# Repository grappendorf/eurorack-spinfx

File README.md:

Eurorack SpinFX
===============

An effects module based on the [Spin FV-1](http://www.spinsemi.com/products.html) IC.

The circuit is built from the reference design in the 
[data sheet](http://www.spinsemi.com/Products/datasheets/spn1001/FV-1.pdf) with some 
standard input and output signal level translation. I've also added a slightly over-engineered 
program number display.

More information can be found on the
[project website](http://www.grappendorf.net/projects/eurorack/eurorack-spinfx.html).

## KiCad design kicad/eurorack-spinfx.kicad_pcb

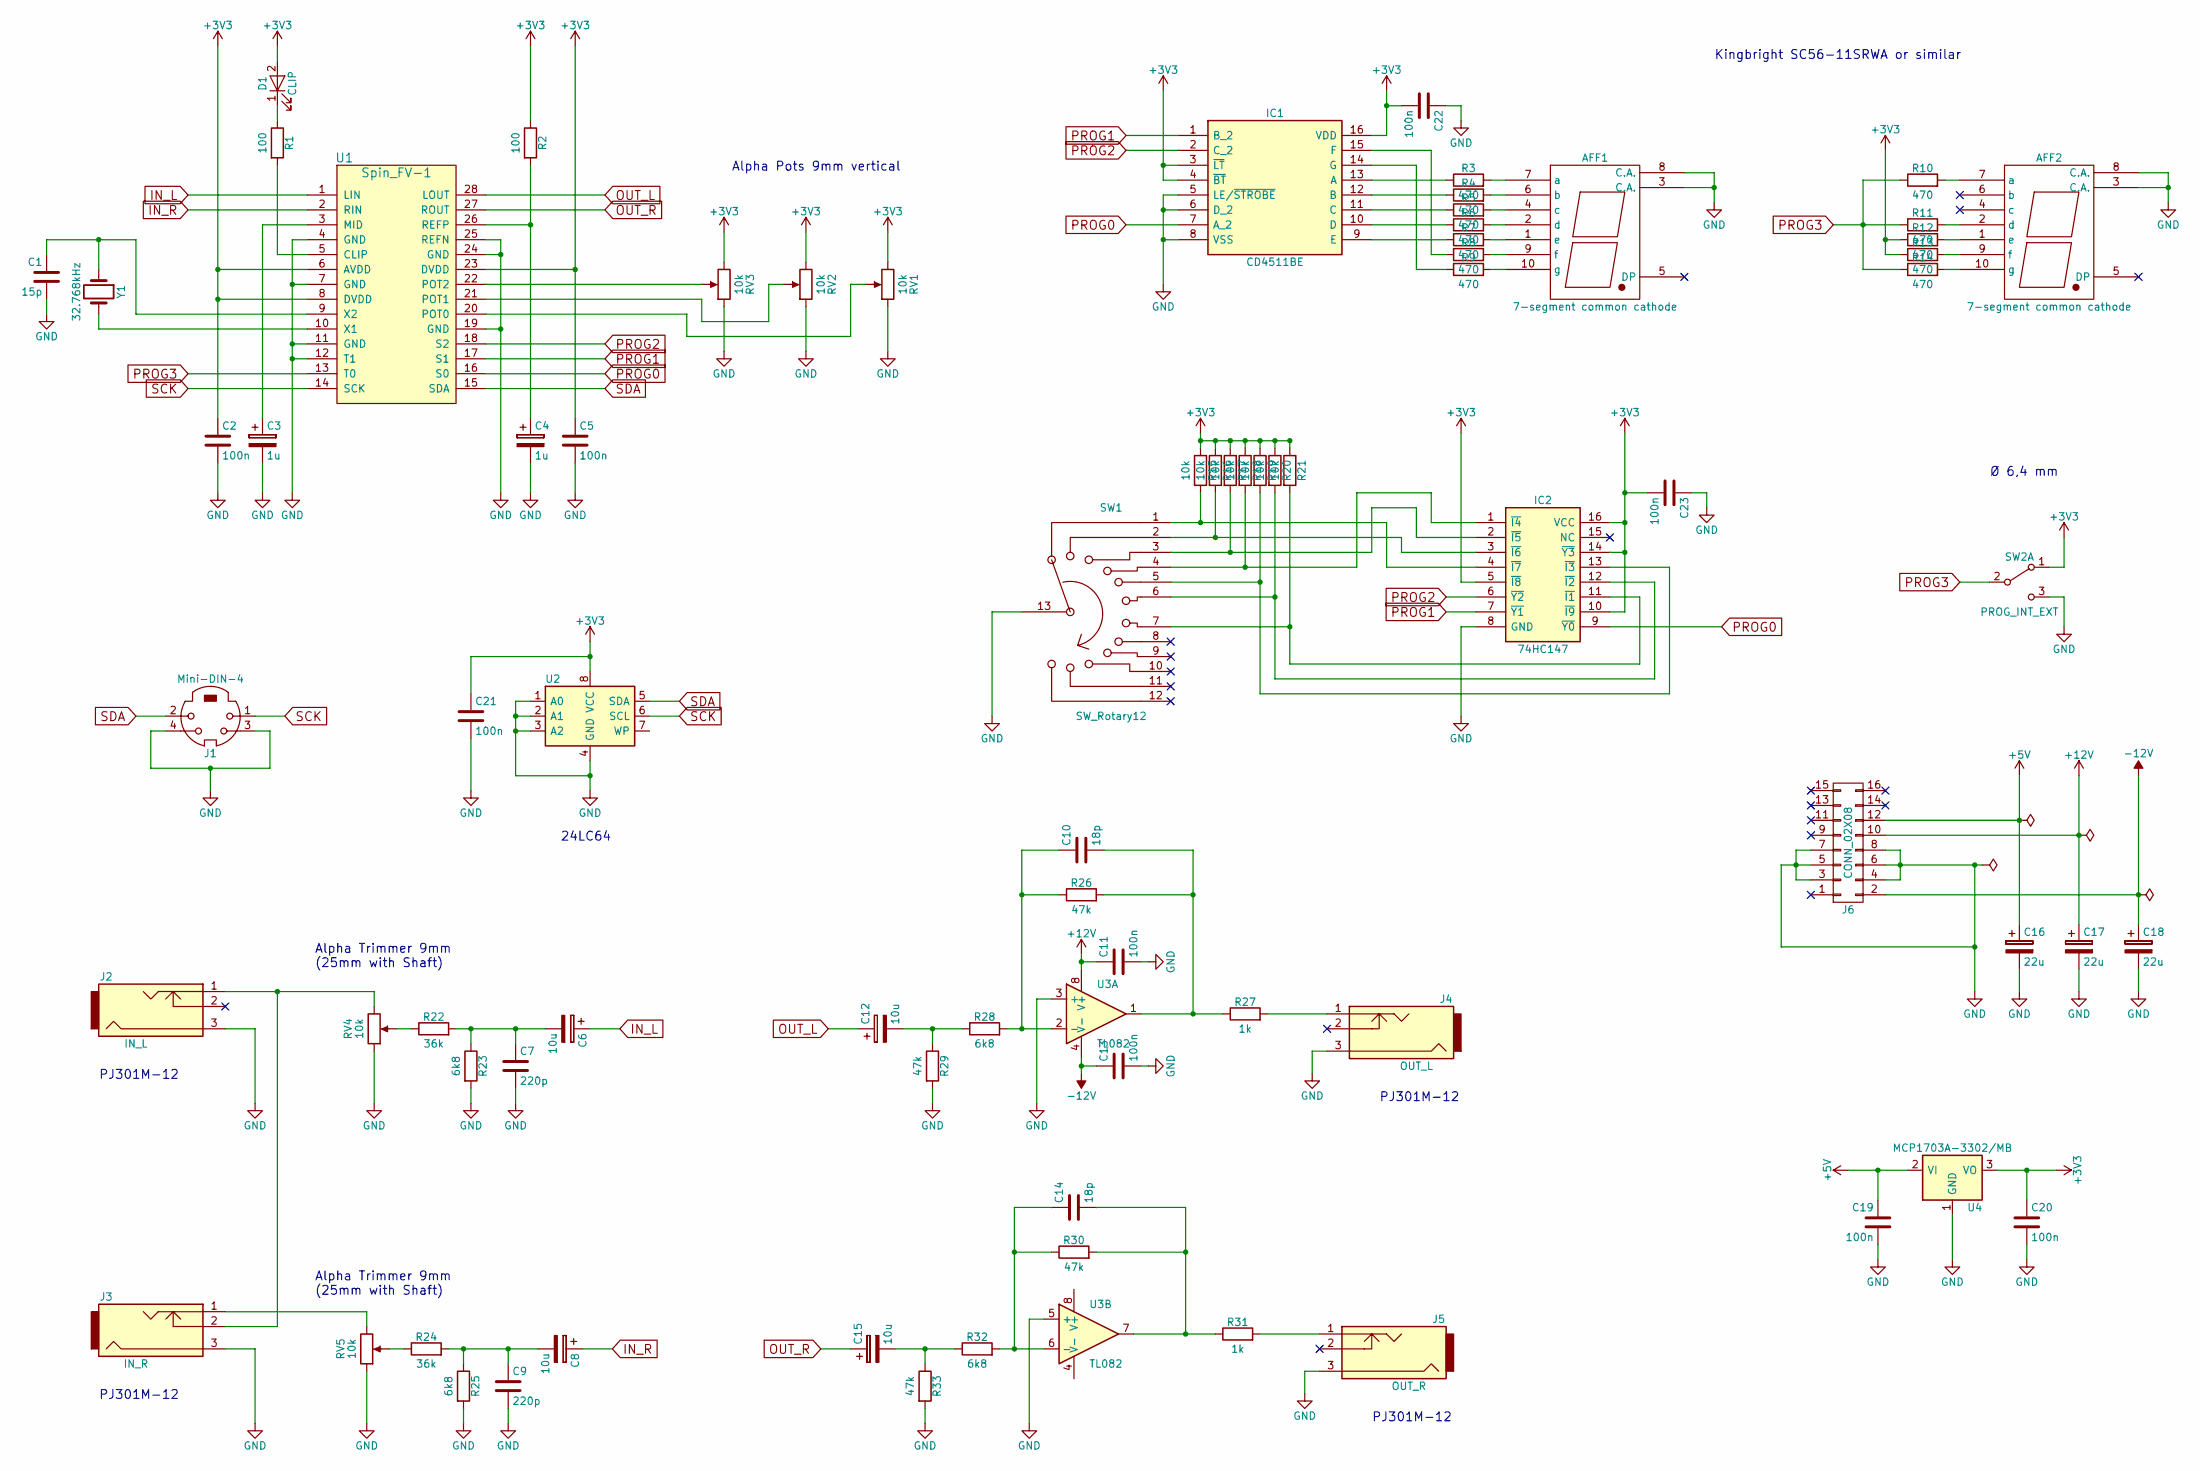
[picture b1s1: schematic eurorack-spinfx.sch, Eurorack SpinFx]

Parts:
AFF1, AFF2: 7-segment common cathode; 7SegmentLED_LTS6760_LTS6780
C1: 15p; C_1206
C2, C5, C11, C13, C19, C20, C21, C22, C23: 100n; C_1206
C3, C4: 1u; CP_Elec_4x5.8
C6, C8, C12, C15: 10u; CP_Elec_4x5.8
C7, C9: 220p; C_1206
C10, C14: 18p; C_1206
C16, C17, C18: 22u; CP_Elec_6.3x5.8
D1: CLIP; LED_D3.0mm
IC1: CD4511BE; SOIC-16_3.9x9.9mm_Pitch1.27mm; Manufacturer_Part_Number CD4511BE
IC2: 74HC147; SOIC-16_3.9x9.9mm_Pitch1.27mm; Manufacturer_Part_Number CD74HC147EE4
J1: Mini-DIN-4; Mini_Din_4
J2: IN_L; PJ301M-12
J3: IN_R; PJ301M-12
J4: OUT_L; PJ301M-12
J5: OUT_R; PJ301M-12
J6: CONN_02X08; Eurorack_Power_2x8_SMD
R1, R2: 100; R_1206
R3, R4, R5, R6, R7, R8, R9, R10, R11, R12, R13, R14: 470; R_1206
R15, R16, R17, R18, R19, R20, R21: 10k; R_1206
R22, R24: 36k; R_1206
R23, R25, R28, R32: 6k8; R_1206
R26, R29, R30, R33: 47k; R_1206
R27, R31: 1k; R_1206
RV1, RV2, RV3: 10k; Alpha_9mm_Pot
RV4, RV5: 10k; Alpha_9mm_Trimmer_25mm_with_Shaft
SW1: SW_Rotary12; ROTARY_SWITCH_LORLINCK1049
SW2: PROG_INT_EXT; Switch_Eledis_1x_On_On
U1: Spin_FV-1; SOIC-28W_7.5x17.9mm_Pitch1.27mm
U2: 24LC64; SO-8_5.3x6.2mm_Pitch1.27mm
U3: TL082; SO-8_5.3x6.2mm_Pitch1.27mm
U4: MCP1703A-3302/MB; SOT-89-3
Y1: 32.768kHz; Crystal_C26-LF_d2.1mm_l6.5mm_Horizontal_1EP_style1

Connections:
+3V3: C2.1, C5.1, C20.1, C21.1, C22.2, C23.2, D1.2 (A), IC1.3 (~LT), IC1.4 (~BT), IC1.16 (VDD), IC2.5 (~I8), IC2.10 (~I9), IC2.14 (~Y3), IC2.16 (VCC), R2.1, R12.1, R13.1, R15.1, R16.1, R17.1, R18.1, R19.1, R20.1, R21.1, RV1.3, RV2.3, RV3.3, SW2.1 (A), U1.6 (AVDD), U1.8 (DVDD), U1.23 (DVDD), U2.8 (VCC), U4.3 (VO)
+5V: C16.1, C19.1, J6.12, U4.2 (VI)
+12V: C11.1, C17.1, J6.10, U3.8 (V+)
-12V: C13.1, C18.1, J6.2, U3.4 (V-)
GND: AFF1.3 (C.A.), AFF1.8 (C.A.), AFF2.3 (C.A.), AFF2.8 (C.A.), C1.2, C2.2, C3.2, C4.2, C5.2, C7.2, C9.2, C11.2, C13.2, C16.2, C17.2, C18.2, C19.2, C20.2, C21.2, C22.1, C23.1, IC1.5 (LE/~STROBE), IC1.6 (D_2), IC1.8 (VSS), IC2.8 (GND), J1.3, J1.4, J2.3, J3.3, J4.3, J5.3, J6.3, J6.4, J6.5, J6.6, J6.7, J6.8, R23.2, R25.2, R29.2, R33.2, RV1.1, RV2.1, RV3.1, RV4.1, RV5.1, SW1.13, SW2.3 (C), U1.4 (GND), U1.7 (GND), U1.11 (GND), U1.12 (T1), U1.19 (GND), U1.24 (GND), U1.25 (REFN), U2.1 (A0), U2.2 (A1), U2.3 (A2), U2.4 (GND), U3.3 (+), U3.5 (+), U4.1 (GND)
IN_L: C6.1, U1.1 (LIN)
IN_R: C8.1, U1.2 (RIN)
unnamed: AFF1.1 (e), R7.2
unnamed: AFF1.2 (d), R6.2
unnamed: AFF1.4 (c), R5.2
unnamed: AFF1.6 (b), R4.2
unnamed: AFF1.7 (a), R3.2
unnamed: AFF1.9 (f), R8.2
unnamed: AFF1.10 (g), R9.2
unnamed: AFF2.1 (e), R12.2
unnamed: AFF2.2 (d), R11.2
unnamed: AFF2.7 (a), R10.2
unnamed: AFF2.9 (f), R13.2
unnamed: AFF2.10 (g), R14.2
unnamed: C1.1, U1.9 (X2), Y1.1
unnamed: C3.1, U1.3 (MID)
unnamed: C4.1, R2.2, U1.26 (REFP)
unnamed: C6.2, C7.1, R22.2, R23.1
unnamed: C8.2, C9.1, R24.2, R25.1
unnamed: C10.1, R26.1, R28.2, U3.2 (-)
unnamed: C10.2, R26.2, R27.1, U3.1
unnamed: C12.2, R28.1, R29.1
unnamed: C14.1, R30.1, R32.2, U3.6 (-)
unnamed: C14.2, R30.2, R31.1, U3.7
unnamed: C15.2, R32.1, R33.1
unnamed: D1.1 (K), R1.1
unnamed: IC1.9 (E), R7.1
unnamed: IC1.10 (D), R6.1
unnamed: IC1.11 (C), R5.1
unnamed: IC1.12 (B), R4.1
unnamed: IC1.13 (A), R3.1
unnamed: IC1.14 (G), R9.1
unnamed: IC1.15 (F), R8.1
unnamed: IC2.1 (~I4), R18.2, SW1.4
unnamed: IC2.2 (~I5), R17.2, SW1.3
unnamed: IC2.3 (~I6), R16.2, SW1.2
unnamed: IC2.4 (~I7), R15.2, SW1.1
unnamed: IC2.11 (~I1), R21.2, SW1.7
unnamed: IC2.12 (~I2), R20.2, SW1.6
unnamed: IC2.13 (~I3), R19.2, SW1.5
unnamed: J2.1, J3.2, RV4.3
unnamed: J3.1, RV5.3
unnamed: J4.1, R27.2
unnamed: J5.1, R31.2
unnamed: R1.2, U1.5 (CLIP)
unnamed: R22.1, RV4.2
unnamed: R24.1, RV5.2
unnamed: RV1.2, U1.20 (POT0)
unnamed: RV2.2, U1.21 (POT1)
unnamed: RV3.2, U1.22 (POT2)
unnamed: U1.10 (X1), Y1.2
OUT_L: C12.1, U1.28 (LOUT)
OUT_R: C15.1, U1.27 (ROUT)
PROG0: IC1.7 (A_2), IC2.9 (~Y0), U1.16 (S0)
PROG1: IC1.1 (B_2), IC2.7 (~Y1), U1.17 (S1)
PROG2: IC1.2 (C_2), IC2.6 (~Y2), U1.18 (S2)
PROG3: R10.1, R11.1, R14.1, SW2.2 (B), U1.13 (T0)
SCK: J1.1, U1.14 (SCK), U2.6 (SCL)
SDA: J1.2, U1.15 (SDA), U2.5 (SDA)

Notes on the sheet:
Alpha Trimmer 9mm (25mm with Shaft)
Alpha Pots 9mm vertical
Kingbright SC56-11SRWA or similar
Ø 6,4 mm
PJ301M-12
24LC64

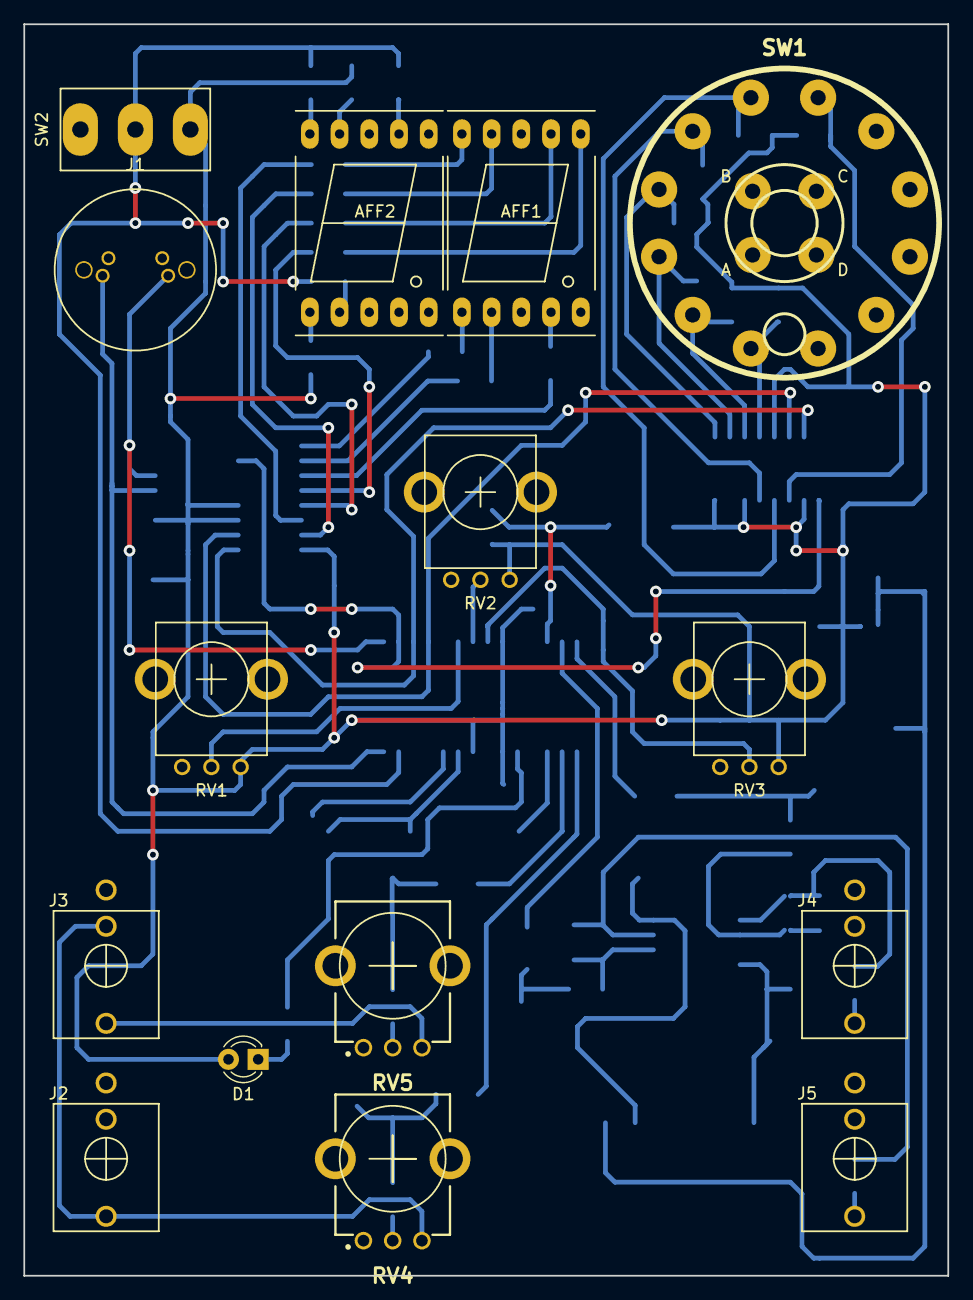
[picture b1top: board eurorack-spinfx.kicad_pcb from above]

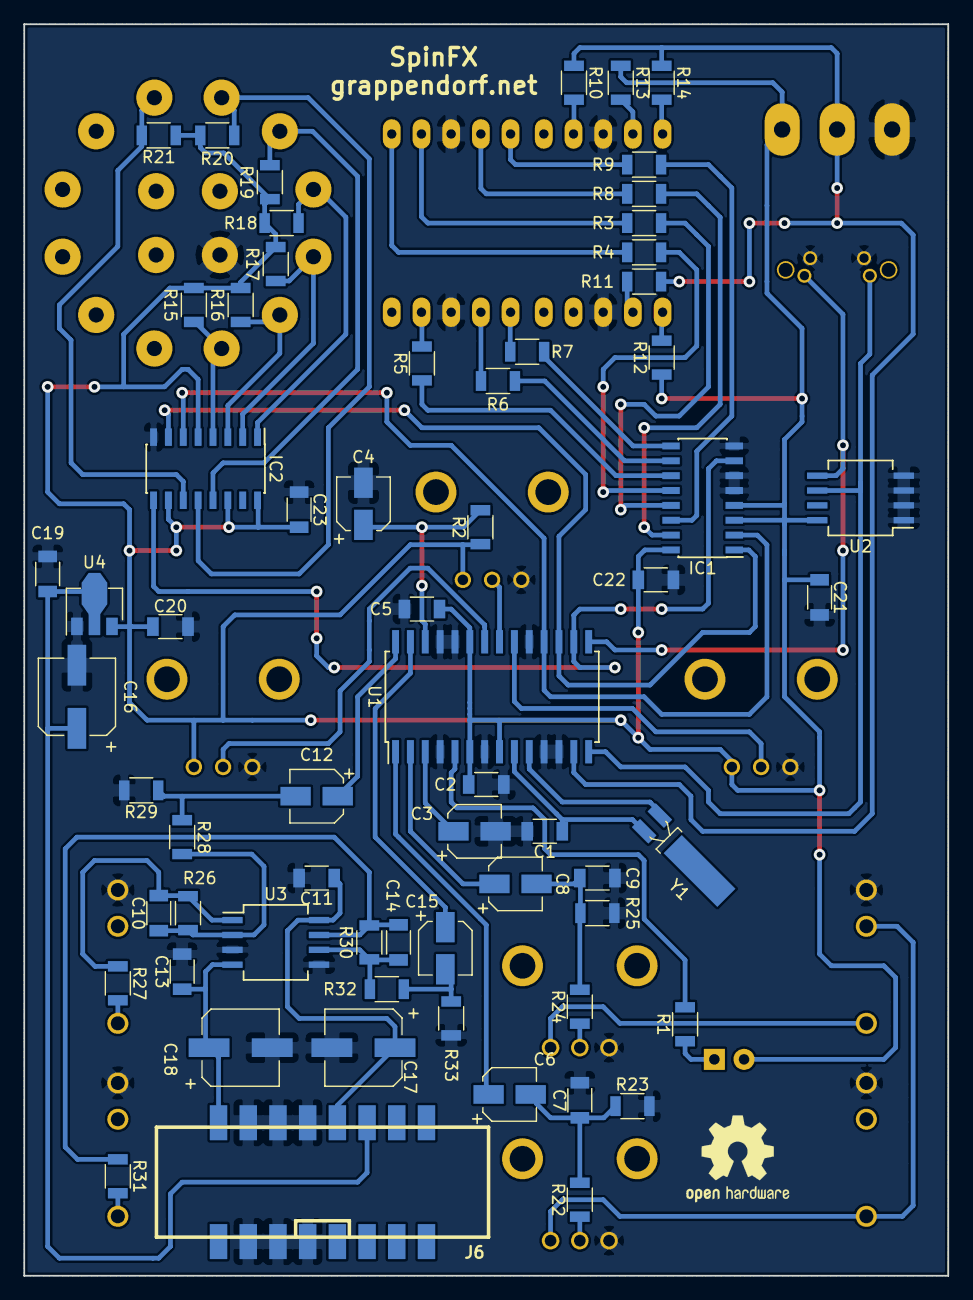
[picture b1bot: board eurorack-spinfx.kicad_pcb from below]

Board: 2 copper layers, 79.0 x 107.0 mm, 79 parts (64 on the bottom side), 64 nets.

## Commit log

2017-11-20 root
2017-11-20 inital commit
2018-10-25 fix typo
